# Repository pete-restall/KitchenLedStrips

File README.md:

# Controller for Under-Cupboard RGB LED Strips

## What is this ?
My wife wanted our new kitchen to have unobtrusive under-cupboard lighting.  It seemed like a simple and relatively quick project so I decided to have
a bash.  Buying off-the-shelf is boring - there's nothing like building something yourself to see why things work as they do or are priced as they are.
This repository is the result of my effort.

### The LED Strips
The LED strips are adhesive-backed tapes stuffed with RGB '5050' LEDs running at 12V and having a single data line.  The data line is essentially an
SPI MOSI with an implicit 800kHz clock configured as a daisy-chain; there is no start bit as is common with other 'clockless' or one-wire protocols so
the data is encoded using pulse-width modulation, a `1` being a long pulse and a `0` being a short pulse.  The tape has 60 LEDs per metre for a power
consumption of 14.4W/m.  Since the supply rail is 12V there are three '5050' LEDs are driven serially with an [SM16703P](doc/datasheets/leds/SM16703P.pdf)
controller providing a constant current of around 17mA.  The [SM16703P](doc/datasheets/leds/SM16703P.pdf) is _similar_ to the more common
[WS2812B](doc/datasheets/leds/WS2812B.pdf).

### The Slave (LED Controller Board)
The controller board I put together is intended to be very simple with few bells and whistles.  It is based around a
[PIC16F15355](doc/datasheets/mcu/PIC16F15355-DS40001853C.pdf) microcontroller.  The controller is fairly dumb in that it is intended as a slave device,
receiving infrared commands via a [TSOP34440](doc/datasheets/infrared/TSOP34440.pdf) and then handling the generation of a frame buffer and its
serialisation onto the wire.  Each controller can output the frame buffer to one or two LED strips over CY 4-core control cable.  Over-current protection
for the LED strip power rail, as well as under- and over-voltage lock-out, are provided, as is a set of GPIO for future expansion.

The circuit was drawn in KiCad and the board was manufactured and assembled by JLCPCB.  To assemble the unit I soldered the through-hole parts (connectors
and wires) to the board and I cut the enclosure faceplates using a CNC router.  The firmware is written in assembly and is built using
[gputils](https://gputils.sourceforge.io/) since I keep forgetting how the Microchip XC8 compiler seems to deliberately produce bad code; redundant
`goto`s to eat cycles, that sort of thing.  The timing of the LED bitstream is tight enough using this microcontroller that such things matter.

### _[WIP]_ The Master (Voice Commands)
The project is being done in two stages.  The first stage is basic on / off control when you flip a switch.  That has been installed already and works
nicely.  The next stage will (the current work-in-progress) aims to allow voice control of the lighting without internet connectivity - no privacy concerns
or failed lighting when the rural broadband takes a dive.  Voice-to-intent _should not need an internet connection_.  Luckily there are frameworks that do
provide this such as one using an
[STM32F405 microcontroller and Picovoice](https://picovoice.ai/blog/offline-voice-assistant-on-an-stm32-microcontroller/)  A proof-of-concept I knocked
up in Python to control some other RGB LEDs in the house via infrared has shown this can work very well, with no model training required.

## The Repository
There are [Board Schematics](src/schematics).

As well as some [Photographs](doc/bench/photos).

There is the [LED Controller Firmware](src/firmware/lights-gadget).

Plus various [Documentation](doc) including [Datasheets](doc/datasheets).

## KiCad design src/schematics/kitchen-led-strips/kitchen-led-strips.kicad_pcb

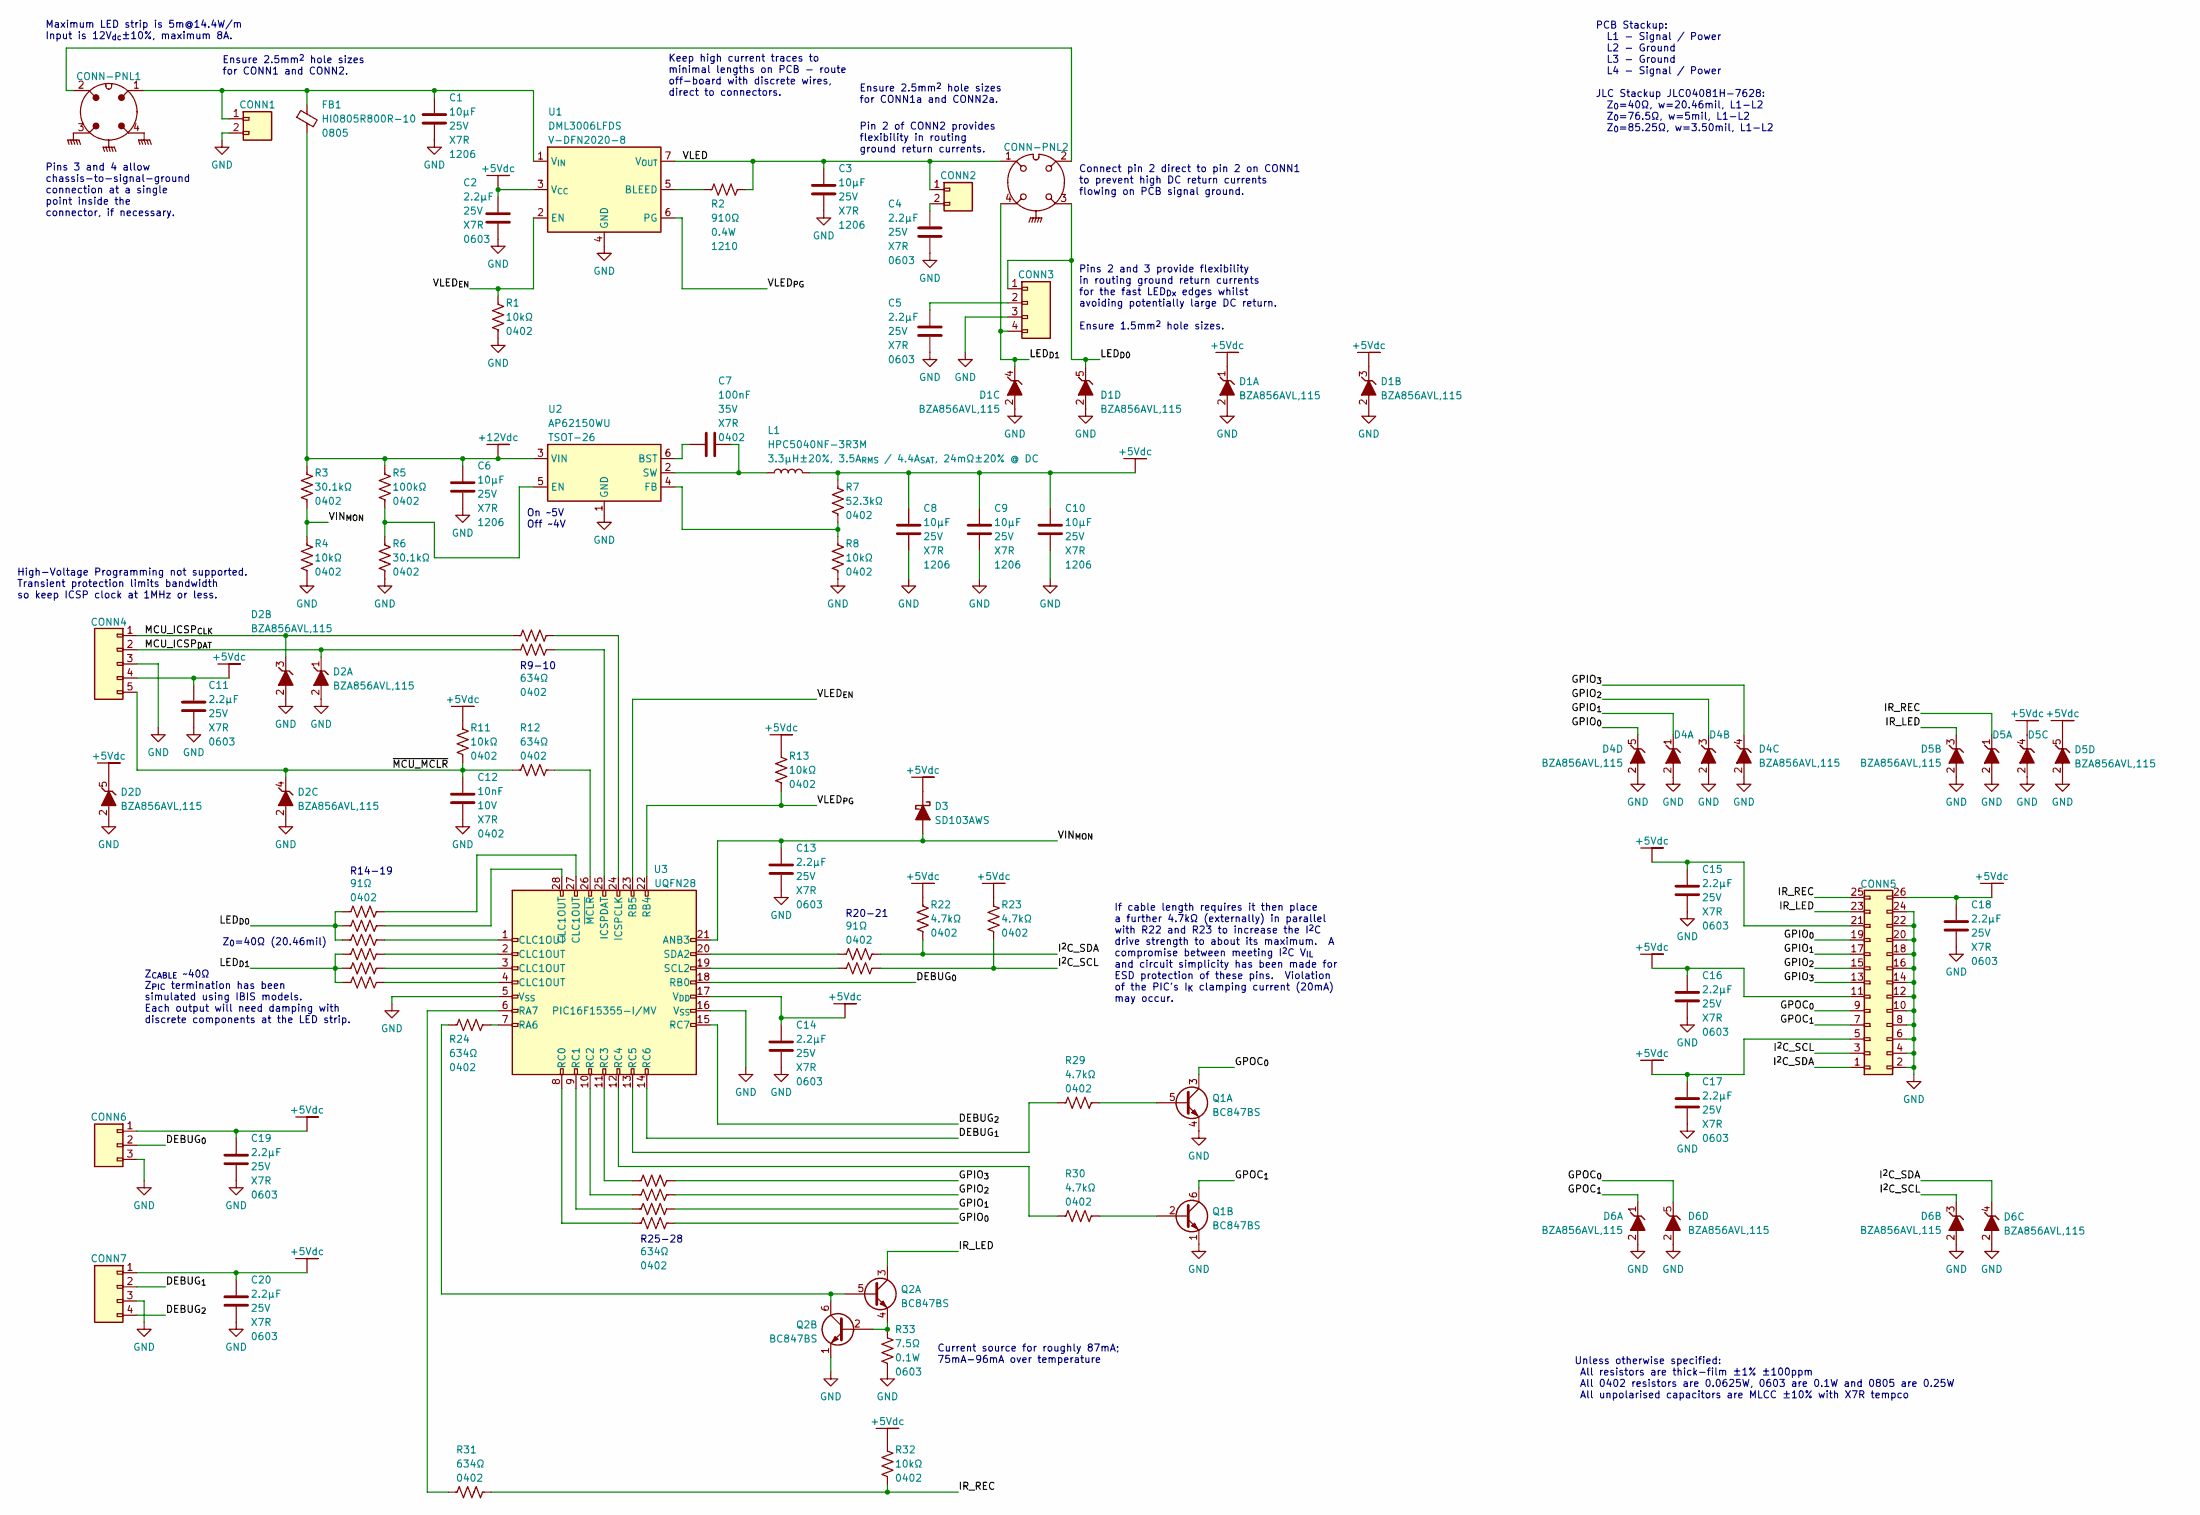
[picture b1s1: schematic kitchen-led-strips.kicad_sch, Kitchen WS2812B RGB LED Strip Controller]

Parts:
C1, C3, C6, C8, C9, C10: 10μF; unpolarised-nominal-1206-3216; Tolerance ±10%; VoltageRating 25V; ManufacturerPartNumber CL31B106KAHNFNE
C2, C4, C5, C11, C13, C14, C15, C16, C17, C18, C19, C20: 2.2μF; unpolarised-nominal-0603-1608; Tolerance ±10%; VoltageRating 25V; ManufacturerPartNumber GRM188Z71E225KE43D
C7: 100nF; unpolarised-nominal-0402-1005; Tolerance ±10%; VoltageRating 35V; ManufacturerPartNumber GRM155R71H104KE14J
C12: 10nF; unpolarised-nominal-0402-1005; Tolerance ±10%; VoltageRating 10V; ManufacturerPartNumber 885012205067
CONN1, CONN2: DNP; th-pads-1x2-5.08mm-vertical-2.5mm^2-solder-pads
CONN3, CONN7: DNP; th-header-1x4-2.54mm-vertical
CONN4: S5B-PH-K-S; S5B-PH-K-?; ManufacturerPartNumber S5B-PH-K-S
CONN5: header-2x13-row; th-header-2x13-2.54mm-row-horizontal-shrouded; ManufacturerPartNumber 19-0045
CONN6: DNP; th-header-1x3-2.54mm-vertical
CONN-PNL1, CONN-PNL2: PSG01593; ManufacturerPartNumber PSG01593
D1, D2, D4, D5, D6: BZA856AVL,115; SOT-353; ManufacturerPartNumber BZA856AVL,115
D3: SD103AWS; SOD-323; ManufacturerPartNumber SD103AWS
FB1: HI0805R800R-10; FB0805; ManufacturerPartNumber HI0805R800R-10
L1: HPC5040NF-3R3M; HPC5040NF; Tolerance ±20%; ManufacturerPartNumber HPC5040NF-3R3M
Q1, Q2: BC847BS; SOT-363; ManufacturerPartNumber BC847BS-7-F
R1, R4, R8, R11, R13, R32: 10kΩ; nominal-0402-1005; Tolerance ±1%; ManufacturerPartNumber RM04F1002CT
R2: 910Ω; nominal-1210-3225; Tolerance ±1%; ManufacturerPartNumber RMCF1210FT910R
R3, R6: 30.1kΩ; nominal-0402-1005; Tolerance ±1%; ManufacturerPartNumber CR0402-FX-3012GLF
R5: 100kΩ; nominal-0402-1005; Tolerance ±1%; ManufacturerPartNumber WR04X1003FTL
R7: 52.3kΩ; nominal-0402-1005; Tolerance ±1%; ManufacturerPartNumber CR0402-FX-5232GLF
R9, R10, R12, R24, R25, R26, R27, R28, R31: 634Ω; nominal-0402-1005; Tolerance ±1%; ManufacturerPartNumber RC0402FR-07634RL
R14, R15, R16, R17, R18, R19, R20, R21: 91Ω; nominal-0402-1005; Tolerance ±1%; ManufacturerPartNumber RC0402FR-0791RL
R22, R23, R29, R30: 4.7kΩ; nominal-0402-1005; Tolerance ±1%; ManufacturerPartNumber WR04X4701FTL
R33: 7.5Ω; nominal-0603-1608; Tolerance ±1%; ManufacturerPartNumber CRCW06037R50FKEA
U1: DML3006LFDS; V-DFN2020-8; ManufacturerPartNumber DML3006LFDS-7
U2: AP62150WU; TSOT-26; ManufacturerPartNumber AP62150WU
U3: PIC16F15355-I/MV; UQFN28-4x4mm-0.4mm-expad-2.35x2.35mm-thermvias; ManufacturerPartNumber PIC16F15355-I/MV

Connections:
+5Vdc: C2.1, C8.1, C9.1, C10.1, C11.1, C14.1, C15.1, C16.1, C17.1, C18.1, C19.1, C20.1, CONN4.4, CONN5.5, CONN5.11, CONN5.21, CONN5.26, CONN6.1, CONN7.1, D1.1 (K), D1.3 (K), D2.5 (K), D3.1 (K), D5.4 (K), D5.5 (K), L1.2 (P2_PWROUT), R7.1, R11.1, R13.1, R22.1, R23.1, R32.1, U1.3 (V_{CC}), U3.17 (V_{DD})
+12V_{dc}: C6.1, FB1.2 (P2_PWROUT), R3.1, R5.1, U2.3 (VIN)
/DEBUG_{0}: CONN6.2, U3.18 (RB0)
/DEBUG_{1}: CONN7.2, U3.14 (RC6)
/DEBUG_{2}: CONN7.4, U3.15 (RC7)
/GPIO_{0}: CONN5.19, D4.5 (K), R28.1
/GPIO_{1}: CONN5.17, D4.1 (K), R27.1
/GPIO_{2}: CONN5.15, D4.3 (K), R26.1
/GPIO_{3}: CONN5.13, D4.4 (K), R25.1
/GPOC_{0}: CONN5.9, D6.5 (K), Q1.3 (C)
/GPOC_{1}: CONN5.7, D6.1 (K), Q1.6 (C)
/IR_LED: CONN5.23, D5.3 (K), Q2.3 (C)
/IR_REC: CONN5.25, D5.1 (K), R31.2, R32.2
/I^{2}C_SCL: CONN5.3, D6.3 (K), R21.1, R23.2
/I^{2}C_SDA: CONN5.1, D6.4 (K), R20.1, R22.2
/LED_{D0}: CONN3.1, CONN-PNL2.3, D1.5 (K), R14.2, R15.2, R16.2
/LED_{D1}: CONN3.4, CONN-PNL2.4, D1.4 (K), R17.2, R18.2, R19.2
/MCU_ICSP_{CLK}: CONN4.1, D2.3 (K), R9.2
/MCU_ICSP_{DAT}: CONN4.2, D2.1 (K), R10.2
/VIN_{MON}: C13.1, D3.2 (A), R3.2, R4.1, U3.21 (ANB3)
/VLED: C3.1, CONN2.1, CONN-PNL2.1, R2.2, U1.7 (V_{OUT}), U1.8 (V_{OUT})
/VLED_{EN}: R1.1, U1.2 (EN), U3.23 (RB5)
/VLED_{PG}: R13.2, U1.6 (PG), U3.22 (RB4)
/~MCU_MCLR: C12.1, CONN4.5, D2.4 (K), R11.2, R12.1
GND: C1.2, C2.2, C3.2, C4.2, C5.2, C6.2, C8.2, C9.2, C10.2, C11.2, C12.2, C13.2, C14.2, C15.2, C16.2, C17.2, C18.2, C19.2, C20.2, CONN1.2 (P2_PWROUT), CONN3.3, CONN4.3, CONN5.2, CONN5.4, CONN5.6, CONN5.8, CONN5.10, CONN5.12, CONN5.14, CONN5.16, CONN5.18, CONN5.20, CONN5.22, CONN5.24, CONN6.3, CONN7.3, D1.2 (A), D2.2 (A), D4.2 (A), D5.2 (A), D6.2 (A), Q1.1 (E), Q1.4 (E), Q2.1 (E), R1.2, R4.2, R6.2, R8.2, R33.2, U1.4 (GND), U2.1 (GND), U3.5 (V_{SS}), U3.16 (V_{SS}), U3.29 (V_{SS})
unnamed: C1.1, CONN1.1, CONN-PNL1.1, FB1.1 (P1_PWRIN), U1.1 (V_{IN}), U1.9 (V_{IN})
unnamed: C4.1, CONN2.2
unnamed: C5.1, CONN3.2
unnamed: C7.1, U2.6 (BST)
unnamed: C7.2, L1.1, U2.2 (SW)
unnamed: CONN-PNL1.2, CONN-PNL2.2
unnamed: CONN-PNL1.3, CONN-PNL1.4
unnamed: Q1.2 (B), R30.2
unnamed: Q1.5 (B), R29.2
unnamed: Q2.2 (B), Q2.4 (E), R33.1
unnamed: Q2.5 (B), Q2.6 (C), R24.1
unnamed: R2.1, U1.5 (BLEED)
unnamed: R5.2, R6.1, U2.5 (EN)
unnamed: R7.2, R8.1, U2.4 (FB)
unnamed: R9.1, U3.24 (ICSPCLK)
unnamed: R10.1, U3.25 (ICSPDAT)
unnamed: R12.2, U3.26 (~MCLR)
unnamed: R14.1, U3.27 (CLC1OUT)
unnamed: R15.1, U3.28 (CLC1OUT)
unnamed: R16.1, U3.1 (CLC1OUT)
unnamed: R17.1, U3.2 (CLC1OUT)
unnamed: R18.1, U3.3 (CLC1OUT)
unnamed: R19.1, U3.4 (CLC1OUT)
unnamed: R20.2, U3.20 (SDA2)
unnamed: R21.2, U3.19 (SCL2)
unnamed: R24.2, U3.7 (RA6)
unnamed: R25.2, U3.11 (RC3)
unnamed: R26.2, U3.10 (RC2)
unnamed: R27.2, U3.9 (RC1)
unnamed: R28.2, U3.8 (RC0)
unnamed: R29.1, U3.13 (RC5)
unnamed: R30.1, U3.12 (RC4)
unnamed: R31.1, U3.6 (RA7)

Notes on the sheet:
Pin 2 of CONN2 provides flexibility in routing ground return currents.
Z_{0}=40Ω (20.46mil)
R20-21
PCB Stackup: L1 - Signal / Power L2 - Ground L3 - Ground L4 - Signal / Power JLC Stackup JLC04081H-7628: Z_{0}=40Ω, w=20.46mil, L1-L2 Z_{0}=76.5Ω, w=5mil, L1-L2 Z_{0}=85.25Ω, w=3.50mil, L1-L2
High-Voltage Programming not supported. Transient protection limits bandwidth so keep ICSP clock at 1MHz or less.
Maximum LED strip is 5m@14.4W/m Input is 12V_{dc}±10%, maximum 8A.
Current source for roughly 87mA; 75mA-96mA over temperature
Unless otherwise specified: All resistors are thick-film ±1% ±100ppm All 0402 resistors are 0.0625W, 0603 are 0.1W and 0805 are 0.25W All unpolarised capacitors are MLCC ±10% with X7R tempco
Pins 2 and 3 provide flexibility in routing ground return currents for the fast LED_{Dx} edges whilst avoiding potentially large DC return. Ensure 1.5mm^{2} hole sizes.
R14-19
Z_{CABLE} ~40Ω Z_{PIC} termination has been simulated using IBIS models. Each output will need damping with discrete components at the LED strip.
Keep high current traces to minimal lengths on PCB - route off-board with discrete wires, direct to connectors.
If cable length requires it then place a further 4.7kΩ (externally) in parallel with R22 and R23 to increase the I^{2}C drive strength to about its maximum. A compromise between meeting I^{2}C V_{IL} and circuit simplicity has been made for ESD protection of these pins. Violation of the PIC's I_{K}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
Connect pin 2 direct to pin 2 on CONN1 to prevent high DC return currents flowing on PCB signal ground.
R9-10
Ensure 2.5mm^{2} hole sizes for CONN1a and CONN2a.
Pins 3 and 4 allow chassis-to-signal-ground connection at a single point inside the connector, if necessary.
R25-28
Ensure 2.5mm^{2} hole sizes for CONN1 and CONN2.
On ~5V Off ~4V

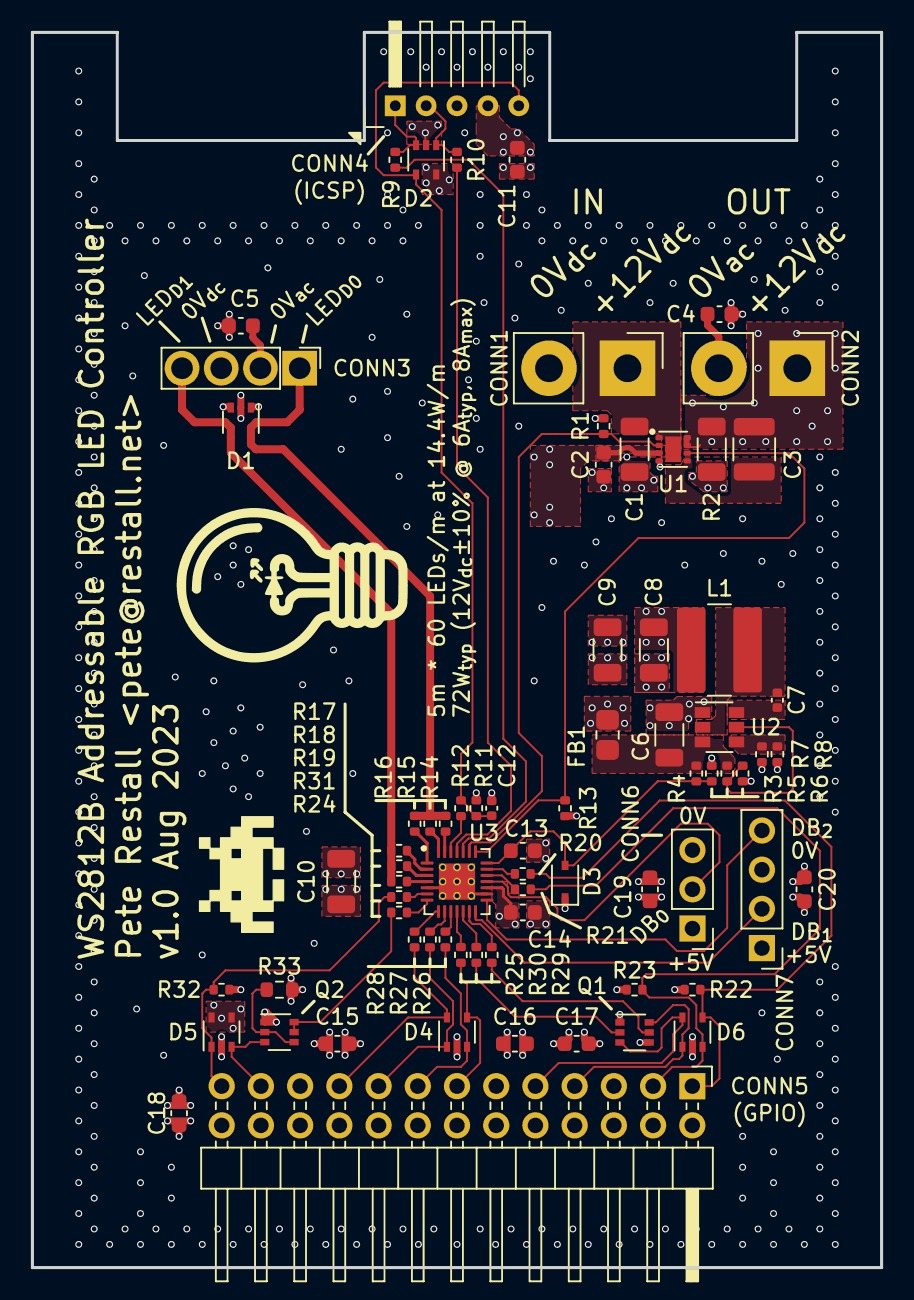
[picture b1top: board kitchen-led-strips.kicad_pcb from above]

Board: 4 copper layers, 55.0 x 80.0 mm, 73 parts (0 on the bottom side), 56 nets.

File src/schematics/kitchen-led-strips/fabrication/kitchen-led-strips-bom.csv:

"Comment","Designator","Footprint","LCSC Part Number"
"VALUE=10μF, PART=CL31B106KAHNFNE (Samsung) or GRM31CR71E106KA12K (Murata)","C1, C3, C6, C8, C9, C10","1206","C307567"
"VALUE=2.2μF, PART=GRM188Z71E225KE43D (Murata) or GRM188Z71E225ME43D (Murata)","C2, C4, C5, C11, C13, C14, C15, C16, C17, C18, C19, C20","0603","C415535"
"VALUE=100nF, PART=GRM155R71H104KE14J (Murata) or GMC04X7R104K50NT (Cal-Chip Electronics)","C7","0402","C2649519"
"VALUE=10nF, PART=885012205067 (Wurth Elektronik) or KGM05AR71E103KH (Kyocera) or CL05B103KB5NNNC (Samsung)","C12","0402","C15195"
"VALUE=BZA856AVL,115, PART=BZA856AVL,115 (Nexperia)","D1, D2, D4, D5, D6","SOT-353","C550063"
"VALUE=SD103AWS, PART=SD103AWS (Anbon Semi) or RB501V-40_R1_00001 (Panjit Semiconductor)","D3","SOD-323","C397613"
"VALUE=HI0805R800R-10, PART=HI0805R800R-10 (Laird Signal Integrity) or WLBD2012HCU121TH (Walsin)","FB1","0805","C3764520"
"VALUE=HPC5040NF-3R3M, PART=HPC5040NF-3R3M (Tai Tech)","L1","HPC5040NF","C357068"
"VALUE=BC847BS, PART=BC847BS-7-F (Diodes Incorporated)","Q1, Q2","SOT-363","C156292"
"VALUE=10kΩ, PART=RM04F1002CT (Cal-Chip Electronics) or RC0402FR-1310KL (Yageo)","R1, R4, R8, R11, R13, R32","0402","C1858459"
"VALUE=910Ω, PART=RMCF1210FT910R (Stackpole Electronics) or RC1210FR-07910RL (Yageo)","R2","1210","C3961717"
"VALUE=30.1kΩ, PART=CR0402-FX-3012GLF (Bourns) or RC0402FR-0730K1L (Yageo)","R3, R6","0402","C138009"
"VALUE=100kΩ, PART=WR04X1003FTL (Walsin) or CR0402-FX-1003GLF (Bourns)","R5","0402","C163806"
"VALUE=52.3kΩ, PART=CR0402-FX-5232GLF (Bourns) or RC0402FR-0752K3L (Yageo)","R7","0402","C2085465"
"VALUE=634Ω, PART=RC0402FR-07634RL (Yageo) or CR0402-FX-6340GLF (Bourns)","R9, R10, R12, R24, R25, R26, R27, R28, R31","0402","C327330"
"VALUE=91Ω, PART=RC0402FR-0791RL (Yageo) or RMCF0402FT91R0 (Stackpole Electronics)","R14, R15, R16, R17, R18, R19, R20, R21","0402","C137926"
"VALUE=4.7kΩ, PART=WR04X4701FTL (Walsin) or RC0402FR-134K7L (Yageo)","R22, R23, R29, R30","0402","C163826"
"VALUE=7.5Ω, PART=CRCW06037R50FKEA (Vishay Dale) or RT0603FRE077R5L (Yageo)","R33","0603","C4022234"
"VALUE=DML3006LFDS, PART=DML3006LFDS-7 (Diodes Incorporated)","U1","V-DFN2020-8","C2149933"
"VALUE=AP62150WU, PART=AP62150WU (Diodes Incorporated)","U2","TSOT-26","C3194237"
"VALUE=PIC16F15355-I/MV, PART=PIC16F15355-I/MV (Microchip)","U3","UQFN28","C637824"

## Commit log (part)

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2023-08-05 Initial commit. Started the schematics and threw together some firmware build files.
2023-08-08 Further elaboration of the schematic.
2023-08-09 Finalised the schematic. Ready for part numbering and checking.
2023-08-09 IBIS simulation for the PIC's output driving the LED cable.
2023-08-09 Schematic tweaks and checks. Added some TODOs for tomorrow.
2023-08-10 Finalised the schematic - checked over and added part numbers. Ready for layout.
2023-08-10 Started work on the PCB.
2023-08-11 Started the PCB layout.
2023-08-12 Further elaboration of the PCB.
2023-08-13 Further PCB elaboration. Almost ready for fabrication.
2023-08-14 Final PCB tweaks. Generated the gerbers for fabrication.
2023-08-14 Added the BOM and placement files for JLCPCB-with-LCSC fabrication.
2023-08-14 Regenerated the schematic's PDF.
2023-08-14 Added a skeleton PWM timer module. Added basic pin initialisation.
2023-08-14 Moved some settings from .vscode into the workspace.
2023-08-17 Added a basic circular buffer implementation.
2023-08-17 Tidied up the workspace a little.
2023-08-17 Added a basic rgbLedsTryShiftNext(r, g, b) function which populates the circular buffer for the UART.
    Unfortunately the UART requires bit reversal (it's LSb-first as opposed to SPI / WS2812B that are MSb-first). Bit reversal is cycle-hungry when there are only 80 cycles between UART bytes to play wit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
    Due to the bit-reversal algorithm being assembler there are some hacks. CMake support for assembler isn't great. The XC8 driver / assembler is 'weird'. The best I could come up with was adding the as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
2023-08-20 Added the datasheet for the actual LED controller contained on my LED strips. Slightly different to the WS2812B.
2023-08-20 Started to add in the modulator for the LEDs but realised that XC8 generates some very inefficient code - at least without the paid-for version. Going to have to rethink this approach.
2023-08-20 Moved the initial stab at a C implementation and bootstrapped a simple (blinky) gpasm-based project. XC8 looked like it deliberately generated slow code (goto goto ???) so hopefully we'll have better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
2023-08-22 Bugfix for merging archives into archives - stdout was also being redirected ! D'oh.
2023-08-22 Started to put together some notes on how the application works. WIP.
2023-08-22 Initial stab at the SM16703P modulator. Basically the UART goes into the CLCs which multiplex between two PWMs for the long and short codes.
2023-08-22 Added a barebones pin and PPS initialisation.
2023-08-22 Added the ISR and circular buffer that are necessary to keep the UART buffer filled at 800kbs.
2023-08-22 A basic power management initialisation routine - default all modules as disabled.
2023-08-22 Added initialisation code for the RGB LEDs module.
2023-08-22 Added the root initialisation module.
2023-08-22 A load of hacks to wire everything together and spit out some colours to an LED strip. Perdy colours. Next step - tidy this up.
2023-08-23 Bugfix for the LED modulator timings - incorrect post-scaler and incorrect clocking edge resulted in starting the output one bit early.
2023-08-23 Added some TODOs to explore the possibility of reclaiming one of the CLCs.
2023-08-23 Added rgbLedsTryPutNextPixel() for appending pixels to the circular buffer. Added rgbLedsStartFrame() for initiating the transmission.
2023-08-25 Fixed some labelling errors / typos on the schematic.
2023-08-25 Fixed the 'off-by-1 bit' modulation error. Also freed up a CLC for other uses.
2023-08-25 Added some initial buffers for the RGB LED frame data.
2023-08-25 Added a basic bit-reversal function.
2023-08-25 Added a function for counting the number of ones in a byte, which will be required for majority voting when over-sampling the output of the infrared receiver with the UART. Also added four (unbanked)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
2023-08-28 Better Identation.
2023-08-28 Added an assembly-time assertion to enforce an assumption that the ISR makes.
2023-08-31 Decreased the WDT to around 4ms, which will cover a single frame.
2023-08-31 Added some TODOs for future requirements.
2023-08-31 Added a basic frame-buffer for 128 RGB LEDs packed into 256 bytes as 5-bit triples. Includes basic gamma correction (y=2.2).
2023-09-01 Bugfix - working registers were allocated as flash ?!?
2023-09-01 Added frame synchronisation and ~32Hz blitting. Currently WIP with some debugging as trying to iron out some wrinkles in the transmission.
2023-09-02 Fixed timing synchronisation between the UART's baud rate generator and the PWM timers. They both derive from Fosc/4 but it looks like the BRG is drifting and causing the number of bits in the first 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
2023-09-02 Slight optimisation to avoid unpacking the RGB components of the current pixel more than once if there was insufficient space in the circular buffer to blit them immediately.
2023-09-02 Reinstated the demo throbber now that the off-by-one bit blitting is sorted. The flicker is gone.
2023-09-02 Smoothed out the gamma correction a little at the low end, since there were multiple values with the same quantisation.
2023-09-02 Added frameBufferClear().
2023-09-02 Added some throbbing for the green and blue LEDs to aid debugging.
2023-09-02 Added a config.pp.asm and config.pp.inc (pp = pre-processing) with a simple sed-based pre-processing script to allow injection of configuration parameters.
2023-09-02 Made the frame-buffer size (ie. number of LEDs) an assembly-time configuration parameter.
    Added rgb-leds/next-pixel.asm to allow code external to the rgb-leds module to fill the frame-buffer in an easy / frame-buffer-agnostic way.
    Removed the throbbing debug code, but that will be shifted elsewhere.
2023-09-03 Added a simple frame counter, incremented once blitting has completed.
2023-09-03 Bugfix - was comparing the FSR0H when should've been FSR0L.
2023-09-03 Minor optimisation - save a couple of instructions per pixel blit.
2023-09-03 Debugging - restored the throbber, this time using the rgbLedsFrameCounter for timing and the rgbLedsTryPutNextPixel() function for updating the frame-buffer.
2023-09-04 Re-timed to a 50Hz frame-rate to allow for interlacing LED values to provide more options for controlling luminance and hue.
2023-09-04 Quick-n-dirty hack to see the effect of interlacing LED values on hue over perceived brightness using our quantised (ie. gamma-corrected) levels.
2023-09-05 Added a basic bicolour interlacing pattern. Needs tweaking as there is some flicker.
2023-09-06 Removed the C project as it's no longer relevant.
2023-09-10 Added in-mmeory palettes for the RGB channels, of which gamma correction is one possibility.
2023-09-10 Fixed typo with number of cycles.
2023-09-10 Added a skeleton module for the infrared transceiver.
2023-09-11 Migrated the LED modulator's reset logic from CLC2 to CLC4. CLC2 is required for modulating the infrared LED on RA6.
2023-09-11 Added a basic IR transceiver. Still WIP so there's some debugging TODOs that need to be sorted out. Also realised that v1.0 of the board has the IR receiver into RA7 but that pin cannot be PPS'd to t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
2023-09-12 Removed the UART TX register (CLC3) from the SM16703P modulator - the timing is such that combinational logic alone works.
    Re-purposed CLC3 as an on-chip bodge wire due to the IR receiver having UART RX wired to RA7 on the board. This is now routed via CLC3 to RB0 (previously DEBUG0) where PPS can take over.
    Added underscore prefices to the private initialisation functions of the SM16703P modulator, to normalise conventions with the other modules.
    Added board-errata.txt to keep track of the hardware issues.
2023-09-12 Moved the 'ir-transceiver' module into a new 'commands' module. Added an irTransceiverTrySend function as well as some irTransceiverOn??? event handlers.
2023-09-12 Fixed the polling return values for the commands and IR transceiver modules.
2023-09-12 Switched from Fosc/4 to HFINTOSC for the frame-sync TIMER0 and fixed the power-saving sleep logic (for the time being).
2023-09-13 Setting UART2's WUE bit just before sleep. Requires a break character of at least 10 bits.
2023-09-13 Added a timeout (of [1, 2] frames, or between [20ms, 40ms]) to the IR receiver so that the state machines can be reset if incomplete packets are received. This also synchronises the 'wakeup' byte.
2023-09-13 Avoiding any side-effects, such as clearing of the pre-scaler counter, that might occur by blithely setting the timer's ON bit.
2023-09-13 Some more timing tweaks.
2023-09-13 Stored the STATUS, PCON0 and PCON1 registers for post-reset inspection and debugging.
2023-09-13 Enabling the Brown-Out Reset.
2023-09-15 Added rgbLeds{Enable,Disable}Blitting() functions to avoid un-necessary LED refreshes.
2023-09-15 Reverting the delay - some bench-testing needs to be done to figure out what this ought to be.
2023-09-15 Added some logic to avoid un-necessary blitting when the colours are static and interlacing is disabled. This logic will not detect changes to the palette.
2023-09-15 Added a basic default colour palette.
2023-09-17 Moved the firmware for the LED controller (slave) into 'lights-gadget' as there is another (master) firmware project, 'go-go-gadget', coming soon.
2023-09-27 Bugfix - missing banksel.
2023-09-27 Switched from a PIC16F15356 as used on the breadboard to a PIC16F15355 now that I have the actual board and have it stood up on the bench.
2023-10-01 Initial stab at CNC models and programs for the enclosure face-plates. WIP.
2023-10-03 Adjustments to the enclosure face-plate models and CNC programs now that they have been machined correctly. Engraving is still to do.
2023-10-04 Adjustments to the enclosure face-plate engraving models and CNC programs now that they have been machined correctly.
2023-10-07 Bugfix - missing banksels.
2023-10-07 The real hardware can't be programmed with a PICKit due to the ESD protection on the programming pins so added a vscode task that copies the firmware to a Raspberry Pi (with an ICSP HAT) and uses pic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
2023-10-11 Started to investigate the filtering required for monitoring the LED voltage but it's actually less work to just do the window comparison on every ADC conversion.
2023-10-13 Added combined build-and-deploy task for quicker / easier debugging on the bench.
2023-10-13 Added a power-supply module that enables / disables the voltage rail for the LEDs. Over-voltage of about 13.5V, under-voltage of about 10V and over-current protection (via the PG pin) are also includ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
2023-10-13 Added builds and skeleton configs for each of the units - one near the fridge, cooker, sink and a debug board. for bench-testing
2023-10-14 Lights to the left- and right-hand-side of the sink are separate.
2023-10-18 Partitioned the frame blitting and added PPS redirection to the appropriate pins. The firmware now supports one or two LED strips using a single frame buffer.
2023-10-18 Added a bunch of measurements looking at the LED data streams with an oscilloscope.
2023-10-19 Initial stab at a swipe-in/out algorithm. Needs to be consolidated. WIP.
2023-10-19 Horrible, but close enough to look alright. Ship it !
2023-10-19 A simpler algorithm that takes into account how the pixels are written by the firmware. Again, not perfect, but good enough.
2023-10-21 Minor tidy-ups.
2023-10-21 Fixed some issues with the blitting algorithm discovered during bench-testing.
2023-10-22 Added a few photographs of the debug unit on the bench.
2023-10-25 Added the option to reverse the order of pixels when blitting the frame-buffer partitions. Some patterns will require this if there are two LED strips depending on their mounting direction.
2023-10-25 Added some more photographs.
2023-10-26 Added a better mechanism for blanking time during power-supply ramp-up. The more granular timing allows us to force-blit the first frame a few milliseconds after the supply is stable without waiting 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
2023-10-26 Not running the (cycle-heavy) code during blitting otherwise the UART TX buffer might not get filled if rgbLedsPoll() is not called frequently enough.
2023-10-26 Had to increase the number of LEDs in the circular buffer since the polling loop is now bogged down. This needs optimising as when, say, the IR LED commands start requiring parsing, this loop is only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
2023-11-01 Added a quick overview of the project.
2023-11-01 Typo.
